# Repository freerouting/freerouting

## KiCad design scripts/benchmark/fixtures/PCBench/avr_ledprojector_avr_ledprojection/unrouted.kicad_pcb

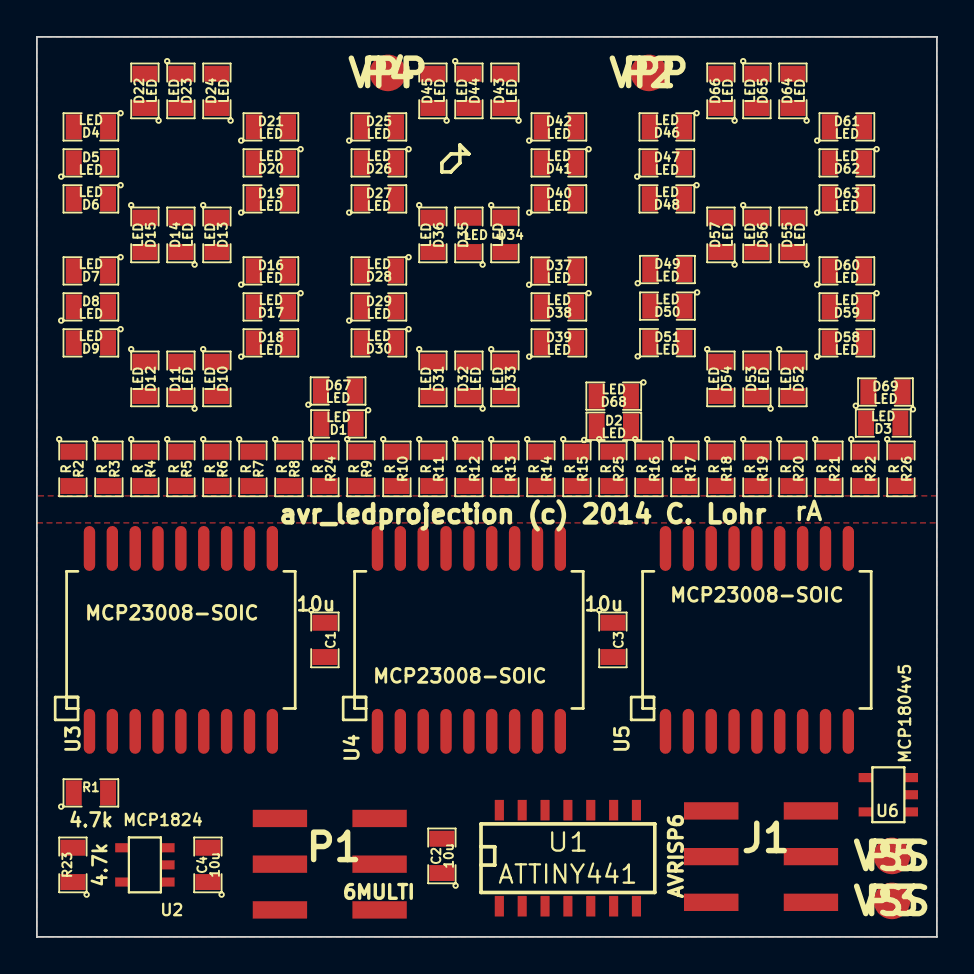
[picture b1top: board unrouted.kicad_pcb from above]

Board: 2 copper layers, 50.0 x 50.0 mm, 111 parts (0 on the bottom side), 104 nets, no tracks yet.

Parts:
C1, C2, C3, C4: 10u; SM0805
D1, D2, D3, D4, D5, D6, D7, D8, D9, D10, D11, D12, D13, D14, D15, D16, D17, D18, D19, D20, D21, D22, D23, D24, D25, D26, D27, D28, D29, D30, D31, D32, D33, D34, D35, D36, D37, D38, D39, D40, D41, D42, D43, D44, D45, D46, D47, D48, D49, D50, D51, D52, D53, D54, D55, D56, D57, D58, D59, D60, D61, D62, D63, D64, D65, D66, D67, D68, D69: LED; SM0805
J1: AVRISP6; RIBBON6SMT
P1: 6MULTI; RIBBON6SMT
P2, P4: VPP; .1SMTPIN
P3, P5: VSS; .1SMTPIN
R1, R23: 4.7k; SM0805
R2, R3, R4, R5, R6, R7, R8, R9, R10, R11, R12, R13, R14, R15, R16, R17, R18, R19, R20, R21, R22, R24, R25, R26: R; SM0805
U1: ATTINY441; SO14E
U2: MCP1824; SOT23-5
U3, U4, U5: MCP23008-SOIC; SOIC18-750
U6: MCP1804v5; SOT23-5

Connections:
+3.3V: C4.1, P1.4, R1.1, R23.1, U2.5
+5V: C1.1, C2.1, C3.1, J1.2, P1.2, U1.1, U2.1, U2.3, U3.4, U3.6, U3.18, U4.5, U4.6, U4.18, U5.6, U5.18, U6.5
GND: C1.2, C2.2, C3.2, C4.2, J1.6, P1.6, P3.1, P5.1, U1.14, U2.2, U3.3, U3.5, U3.9, U4.3, U4.4, U4.9, U5.3, U5.4, U5.5, U5.9, U6.2
unnamed: R9.2, U4.17
unnamed: R11.2, U4.15
unnamed: R22.2, U5.11
unnamed: R20.2, U5.13
unnamed: R18.2, U5.15
unnamed: R16.2, U5.17
unnamed: R4.2, U3.15
unnamed: R2.2, U3.17
unnamed: D3.1, D69.2
unnamed: R15.2, U4.11
unnamed: R25.2, U4.10
unnamed: D3.2, R26.1
unnamed: R26.2, U5.10
unnamed: D2.2, R25.1
unnamed: R7.2, U3.12
unnamed: D1.2, R24.1
unnamed: R24.2, U3.10
unnamed: J1.4, U1.7
unnamed: R21.2, U5.12
unnamed: P1.5, U1.11
unnamed: J1.1, U1.8
unnamed: R8.2, U3.11
unnamed: J1.5, U1.4
unnamed: J1.3, U1.9
unnamed: D2.1, D68.2
unnamed: D1.1, D67.2
unnamed: D44.2, D45.1
unnamed: D45.2, R15.1
unnamed: D46.2, D47.1
unnamed: D47.2, D48.1
unnamed: D43.2, D44.1
unnamed: D48.2, R16.1
unnamed: D49.2, D50.1
unnamed: D50.2, D51.1
unnamed: D51.2, R17.1
unnamed: R13.2, U4.13
unnamed: D36.2, R12.1
unnamed: R12.2, U4.14
unnamed: D37.2, D38.1
unnamed: D38.2, D39.1
unnamed: D39.2, R13.1
unnamed: R17.2, U5.16
unnamed: D40.2, D41.1
unnamed: D41.2, D42.1
unnamed: D42.2, R14.1
unnamed: R14.2, U4.12
unnamed: D60.2, R20.1
unnamed: D61.2, D62.1
unnamed: D62.2, D63.1
unnamed: D63.2, R21.1
unnamed: D64.2, D65.1
unnamed: D65.2, D66.1
unnamed: D66.2, R22.1
unnamed: D52.2, D53.1
unnamed: D53.2, D54.1
unnamed: D54.2, R18.1
unnamed: D55.2, D56.1
unnamed: D56.2, D57.1
unnamed: D57.2, R19.1
unnamed: R19.2, U5.14
unnamed: D58.2, D59.1
unnamed: D59.2, D60.1
unnamed: D13.2, D14.1
unnamed: D14.2, D15.1
unnamed: D15.2, R5.1
unnamed: R5.2, U3.14
unnamed: D12.2, R4.1
unnamed: D16.2, D17.1
unnamed: D17.2, D18.1
unnamed: D18.2, R6.1
unnamed: R6.2, U3.13
unnamed: D4.2, D5.1
unnamed: D5.2, D6.1
unnamed: D6.2, R2.1
unnamed: D7.2, D8.1
unnamed: D19.2, D20.1
unnamed: D8.2, D9.1
unnamed: D9.2, R3.1
unnamed: D10.2, D11.1
unnamed: D11.2, D12.1
unnamed: D28.2, D29.1
unnamed: D29.2, D30.1
unnamed: D30.2, R10.1
unnamed: R10.2, U4.16
unnamed: D31.2, D32.1
unnamed: D32.2, D33.1
unnamed: D33.2, R11.1
unnamed: D34.2, D35.1
unnamed: D35.2, D36.1
unnamed: D20.2, D21.1
unnamed: D21.2, R7.1
unnamed: D22.2, D23.1
unnamed: D23.2, D24.1
unnamed: D24.2, R8.1
unnamed: D25.2, D26.1
unnamed: D26.2, D27.1
unnamed: D27.2, R9.1
unnamed: R3.2, U3.16
SCL: P1.3, R23.2, U1.13, U3.1, U4.1, U5.1
SDA: P1.1, R1.2, U1.12, U3.2, U4.2, U5.2
VPP: D4.1, D7.1, D10.1, D13.1, D16.1, D19.1, D22.1, D25.1, D28.1, D31.1, D34.1, D37.1, D40.1, D43.1, D46.1, D49.1, D52.1, D55.1, D58.1, D61.1, D64.1, D67.1, D68.1, D69.1, P2.1, P4.1, U6.1, U6.4

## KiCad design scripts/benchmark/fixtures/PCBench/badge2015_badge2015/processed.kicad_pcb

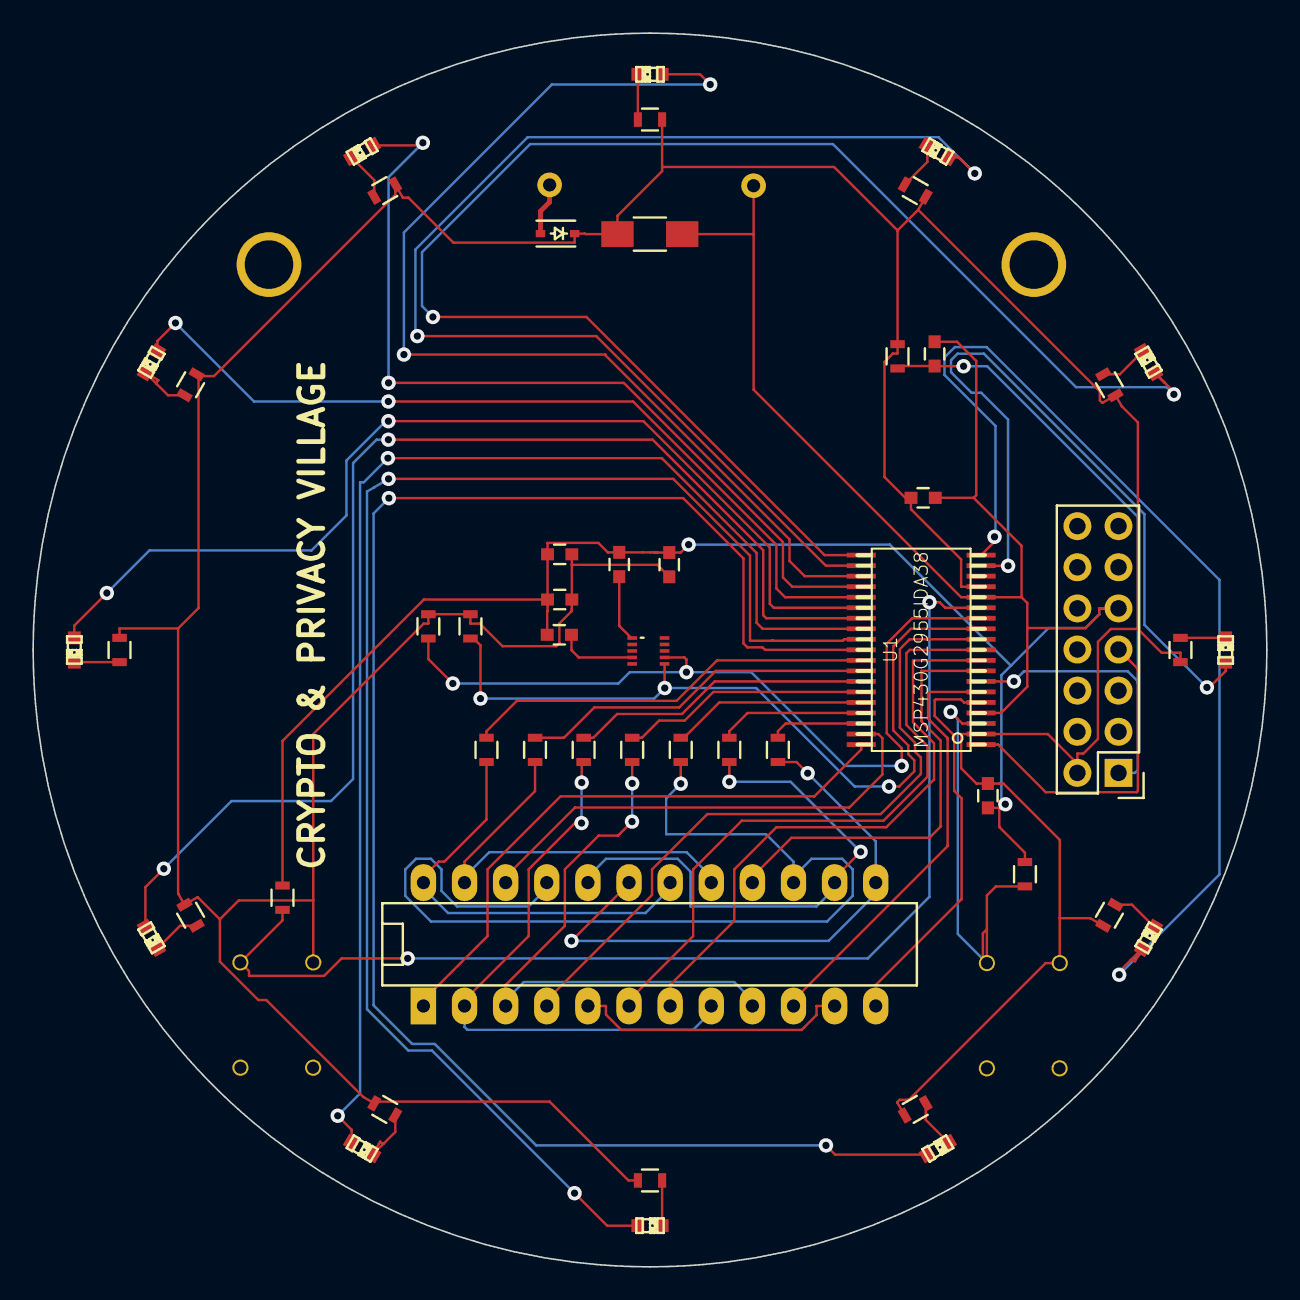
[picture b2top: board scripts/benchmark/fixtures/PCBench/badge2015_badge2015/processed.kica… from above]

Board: 2 copper layers, 76.2 x 76.2 mm, 55 parts (1 on the bottom side), 58 nets.

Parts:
2.2nF1: C; C_0603
BT1: Battery
C1, C2: 0.1uf; C_0603
C6: 47uF; C_1206_HandSoldering
C7: 1uf; C_0603
C8, C9, C10, C11: 100nf; C_0603
D1, D2, D3, D4, D5, D6, D7, D8, D9, D10, D11, D12: LED; LED-0603
D55: DIODE; SOD-323
MAG: MAG3110_10VFDFN
P1: CONN_01X14; Pin_Header_Straight_2x07
R1, R2, R3, R4, R5, R6, R7, R8, R9, R10, R11, R12: 499; R_0603
R13, R23: R; R_0603
R14, R15, R16, R17, R18, R21, R22: 680; R_0603
R19, R20: 4.7k; R_0603
R24: 47k; R_0603
SW1, SW2: SW_PUSH; push_btn
U1: MSP430G2955IDA38; AB2_TSSOP38_W
U4: 7SEGMENT; DIP-24__300_ELL
hole_l: hole
hole_r: hole_r; hole

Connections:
/3.3V: C1.1, C2.1, C6.1, C7.1, C8.1, C11.1, D55.2, P1.2, R1.1, R2.1, R3.1, R4.1, R5.1, R6.1, R7.1, R8.1, R9.1, R10.1, R11.1, R12.1, R19.1, R20.1, R24.1, SW1.1, SW2.1, U1.2, U1.16
/ANODE_a: R14.2, U4.12, U4.24
/ANODE_b: R15.2, U4.11, U4.23
/ANODE_c: R17.2, U4.3, U4.15
/ANODE_d: R21.2, U4.8, U4.20
/ANODE_dp: U4.5, U4.17
/ANODE_e: R16.2, U4.2, U4.14
/ANODE_f: R18.2, U4.9, U4.21
/ANODE_g: R22.2, U4.7, U4.19
/BAT+: BT1.1, D55.1
/CATHODE_1: U1.38, U4.1
/CATHODE_2: U1.37, U4.10
/CATHODE_3: U1.11, U4.4
/CATHODE_4: U1.10, U4.6
/CATHODE_5: U1.9, U4.13
/CATHODE_6: U1.8, U4.22
/CATHODE_7: U1.6, U4.16
/CATHODE_8: U1.5, U4.18
/P1(0): R15.1, U1.31
/P1(1): R16.1, U1.32
/P1(2): R17.1, U1.33
/P1(3): R18.1, U1.34
/P1(4): R21.1, U1.35
/P1(5): R22.1, U1.36
/P2(3): D2.2, U1.29
/P2(4): R14.1, U1.30
/P2(5): R13.1, SW1.2, U1.3
/P3(3): R23.1, SW2.2, U1.14
/P3(4): D10.2, U1.25
/P3(5): D11.2, U1.26
/P3(6): D12.2, U1.27
/P3(7): D1.2, U1.28
/P4(1): D4.2, U1.18
/P4(2): D3.2, U1.19
/P4(3): D5.2, U1.20
/P4(4): D6.2, U1.21
/P4(5): D7.2, U1.22
/P4(6): D8.2, U1.23
/P4(7): D9.2, U1.24
/SBWTCK: P1.7, U1.1
/SCL: MAG.7, R20.2, U1.13
/SDA: MAG.6, R19.2, U1.12
/~RST: 2.2nF1.1, P1.1, R24.2, U1.7
GND: 2.2nF1.2, BT1.2, C1.2, C2.2, C6.2, C7.2, C8.2, C9.1, C10.2, C11.2, P1.9, R13.2, R23.2, U1.4, U1.15
unnamed: C9.2, MAG.1
unnamed: C10.1, MAG.4
unnamed: D1.1, R1.2
unnamed: D2.1, R2.2
unnamed: D3.1, R3.2
unnamed: D4.1, R4.2
unnamed: D5.1, R5.2
unnamed: D6.1, R6.2
unnamed: D7.1, R7.2
unnamed: D8.1, R8.2
unnamed: D9.1, R9.2
unnamed: D10.1, R10.2
unnamed: D11.1, R11.2
unnamed: D12.1, R12.2

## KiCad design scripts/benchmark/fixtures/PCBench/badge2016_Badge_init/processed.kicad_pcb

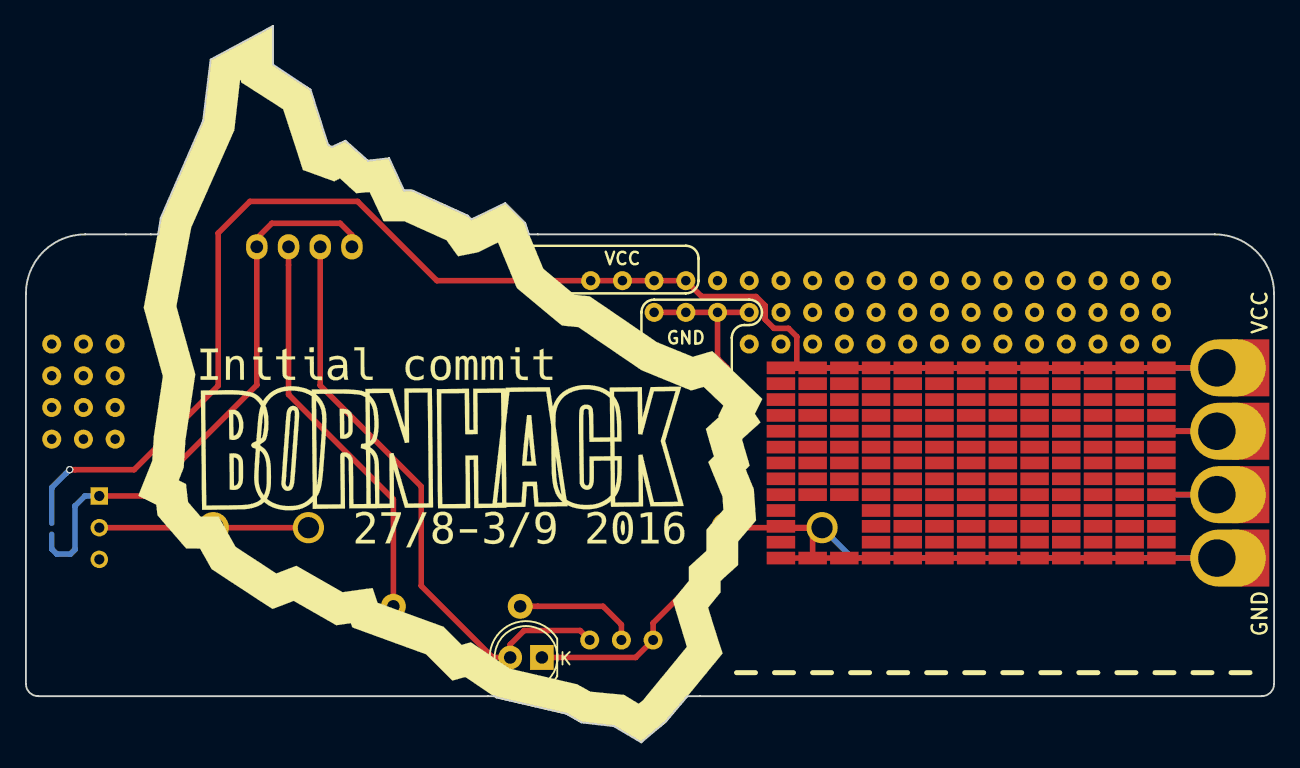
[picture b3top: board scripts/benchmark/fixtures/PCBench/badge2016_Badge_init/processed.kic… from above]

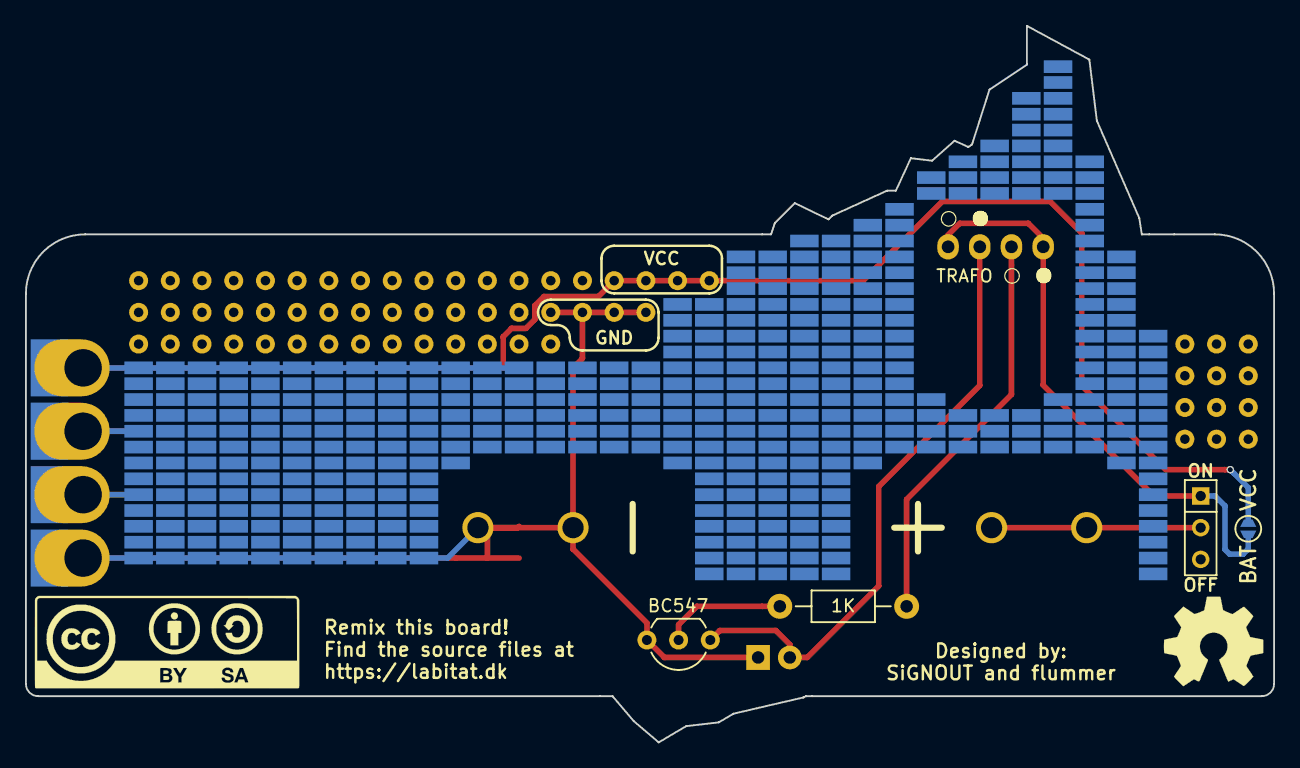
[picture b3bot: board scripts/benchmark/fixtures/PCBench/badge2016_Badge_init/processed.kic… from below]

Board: 2 copper layers, 100.0 x 57.4 mm, 9 parts (6 on the bottom side), 6 nets.

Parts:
BT1: Battery; BK-92
D1: LED; LED-5MM
JP1: Jumper_NC_Small; Solder_Jumper
P1, P2: CONN_01X01; PTH_Edge_Proto_Connector
Q1: BC547; TO-92_Inline_Wide
R1: 1K; Resistor_Horizontal_RM10mm
SW1: POWER; SW_Micro_SPST
T1: TRAFO; Pin_Header_Straight_1x04

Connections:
+BATT: JP1.1, SW1.1, T1.1, T1.4
GND: BT1.2, D1.1, Q1.3
unnamed: BT1.1, SW1.2
unnamed: D1.2, Q1.1, T1.3
unnamed: Q1.2, R1.2
unnamed: R1.1, T1.2

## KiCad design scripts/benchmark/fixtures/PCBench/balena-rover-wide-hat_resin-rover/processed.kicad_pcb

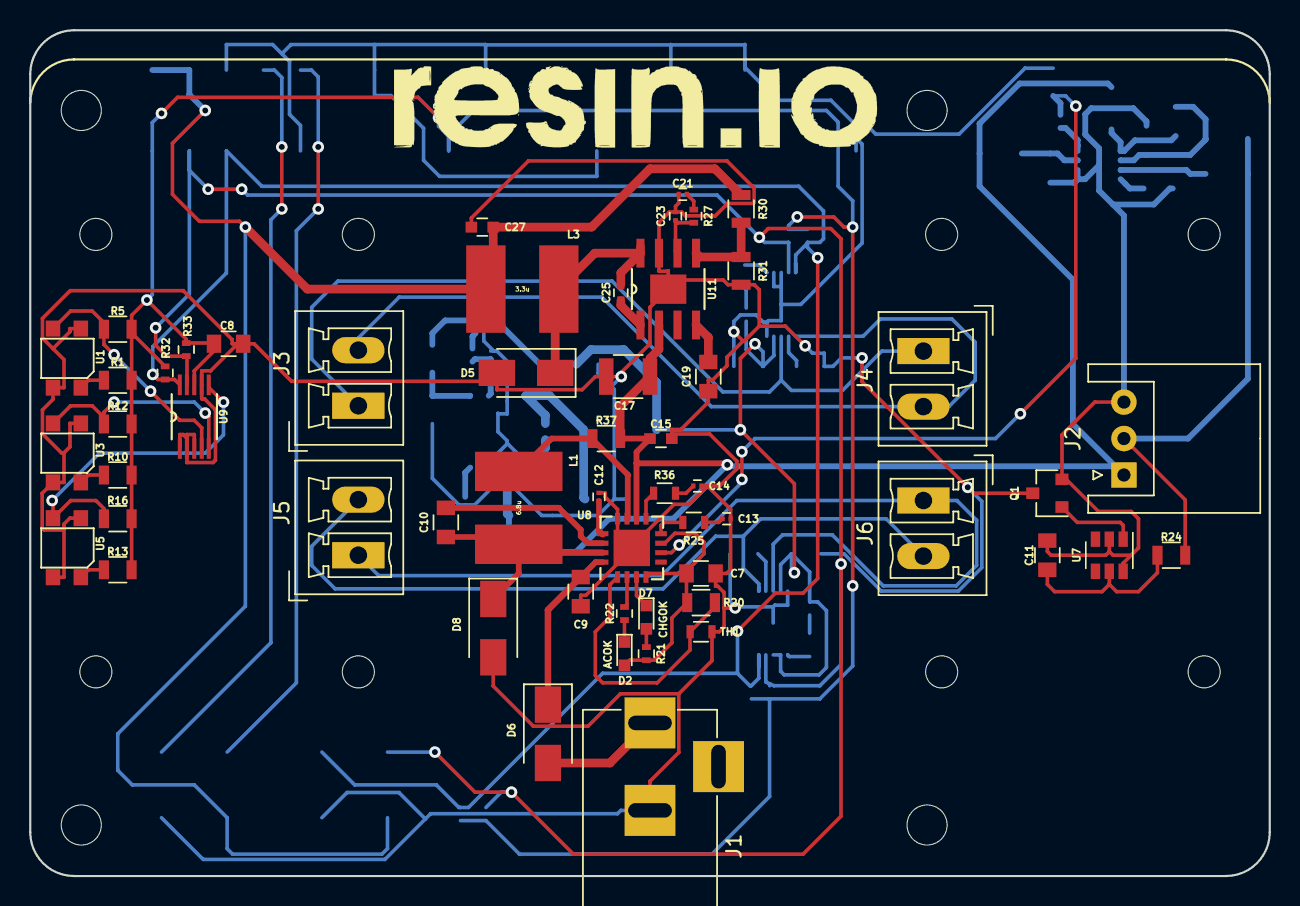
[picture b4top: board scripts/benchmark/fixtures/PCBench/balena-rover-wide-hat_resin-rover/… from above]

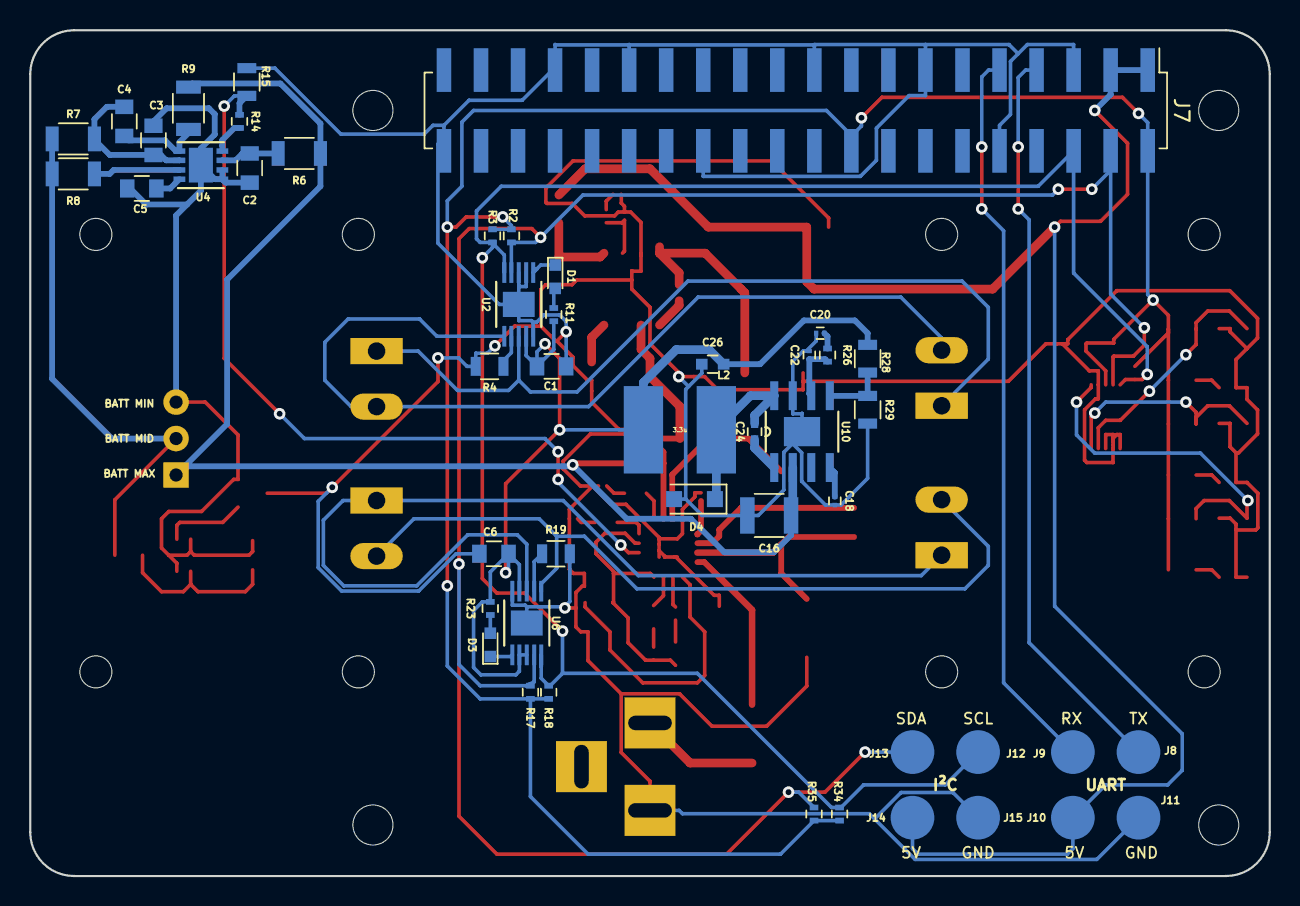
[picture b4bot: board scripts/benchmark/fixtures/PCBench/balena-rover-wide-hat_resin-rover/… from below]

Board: 2 copper layers, 85.0 x 58.0 mm, 107 parts (48 on the bottom side), 64 nets.

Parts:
C1, C6: 10u; C_0805
C2, C3, C4, C5, C8, C10, C11: 0.1u; C_0805
C7: 1u; C_0805
C9: 4.7u; C_0805
C12: 0.1u; C_0201
C13, C14: 2.2n; C_0201
C15, C26, C27: 22u; C_0603
C16, C17: 22u; C_1210
C18: 27p; C_0201
C19: 30p; C_0805
C20: 1n; C_0201
C21: 1.2n; C_0201
C22, C23: 8.2n; C_0201
C24, C25: 100n; C_0402
D1, D2, D3, D7: LED; LED_0603
D4: D_Schottky; D_SOD-123F
D5: D_Schottky; D_SMA_Standard
D6, D8: Schottky; D_SMA_Standard
J1: BARREL_JACK
J2: 2S LIPO; JST_XH_S03B-XH-A_03x2.50mm_Angled
J3: FL; PhoenixContact_MCV-G_02x3.81mm_Vertical
J4: BL; PhoenixContact_MCV-G_02x3.81mm_Vertical
J5: FR; PhoenixContact_MCV-G_02x3.81mm_Vertical
J6: BR; PhoenixContact_MCV-G_02x3.81mm_Vertical
J7: CONN_02X20; Pin_Header_Straight_2x20_Pitch2.54mm_SMD
J8, J9, J10, J11, J12, J13, J14, J15: TEST_1P; Measurement_Point_Round-SMD-Pad_Big
L1: 6.8u; SRN6045
L2, L3: 3.3u; SRN6045
Noname_1, Noname_2, Noname_3, Noname_4: RPi_Hat_Mounting_Hole
Q1: 2N7002; SOT-23
R1, R10, R13: 100; R_0805
R2, R3, R14, R17, R18, R32, R33, R34, R35: 4.7K; R_0402
R4, R19: 0.2; R_0805
R5, R12, R15, R16, R20, R24, R28: 10K; R_0805
R6, R8, R9: 150; R_1206
R7: 240; R_1206
R11, R21, R22, R23: 1K; R_0402
R25: 2.49K; R_0603
R26: 30.1K; R_0402
R27: 26.7K; R_0402
R29: 1.54K; R_0805
R30: 10.5K; R_0805
R31: 2K; R_0805
R36: 750; R_0603
R37: 0.1; R_0805
TH1: NTC 10K; R_0603
U1, U3, U5: QRE1113GR; 4LEADSMD
U2, U6: DRV8830; SOP65P640X110-15N
U4: BQ29209; SON65P315X315X100-9N
U7: S-8261; SOT-23-6
U8: MP2610; QFN-16-1EP_4x4mm_Pitch0.65mm
U9: ADS1015; SOP50P490X110-10N
U10, U11: TPS54332; SOIC127P600X170-9N

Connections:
/3.3V: C8.2, J7.2, J7.18, R1.2, R2.2, R3.2, R5.2, R10.2, R12.2, R13.2, R16.2, R17.2, R18.2, R32.1, R33.2, R34.2, R35.2, U9.8
/5V: C27.2, J7.1, J7.3, J10.1, J14.1, L3.1, R30.2
/6V: C1.1, C6.1, C26.2, L2.1, R11.1, R23.2, R28.2, U2.4, U6.4, U6.7, U6.8
/ADC0: R5.1, U1.C, U9.4
/ADC1: R12.1, U3.C, U9.5
/ADC2: R16.1, U5.C, U9.6
/BATT_MID: J2.2, R7.2, R8.2, R24.2
/BATT_MIN: C2.2, C3.1, C5.2, C11.2, J2.3, Q1.2, U4.5, U4.6, U4.9, U7.2, U7.6
/CHG_EN: R14.2, R15.1, U8.6
/DO: Q1.1, U7.1
/VCC: D6.2, J1.1
/VSENSE_5V: R30.1, R31.2, U11.5
/VSENSE_6V: R28.1, R29.2, U10.5
/V_BATT: C15.2, C16.2, C17.2, J2.1, R6.1, R9.2, R37.1, U8.10, U10.2, U11.2
GND: C1.2, C6.2, C7.1, C8.1, C9.2, C12.1, C13.1, C14.1, C15.1, C16.1, C17.1, C18.1, C19.1, C20.1, C21.1, C22.1, C23.1, C26.1, C27.1, D4.2, D5.2, D8.2, J1.2, J7.5, J7.10, J7.13, J7.19, J7.26, J7.29, J7.33, J7.40, J11.1, J15.1, Q1.3, R4.2, R15.2, R19.2, R29.1, R31.1, TH1.2, U1.E, U1.K, U2.5, U2.7, U2.8, U2.11, U3.E, U3.K, U5.E, U5.K, U6.5, U6.11, U8.12, U8.17, U9.1, U9.2, U9.3, U9.7, U10.7, U10.9, U11.7, U11.9
unnamed: C2.1, R6.2, U4.7
unnamed: C3.2, C4.2, R7.1, U4.2
unnamed: C4.1, R9.1, U4.1
unnamed: C5.1, U4.4
unnamed: C7.2, D2.2, R20.2, R21.1, U8.4, U8.7
unnamed: C9.1, D6.1, U8.16
unnamed: C10.1, D8.1, L1.2, U8.15
unnamed: C10.2, U8.14
unnamed: C11.1, R24.1, U7.5
unnamed: C12.2, U8.13
unnamed: C13.2, R25.1
unnamed: C14.2, R36.1
unnamed: C18.2, U10.4
unnamed: C19.2, U11.4
unnamed: C20.2, R26.1
unnamed: C21.2, R27.1
unnamed: C22.2, R26.2, U10.6
unnamed: C23.2, R27.2, U11.6
unnamed: C24.1, D4.1, L2.2, U10.8
unnamed: C24.2, U10.1
unnamed: C25.1, D5.1, L3.2, U11.8
unnamed: C25.2, U11.1
unnamed: D1.1, U2.6
unnamed: D1.2, R11.2
unnamed: D2.1, R22.2
unnamed: D3.1, U6.6
unnamed: D3.2, R23.1
unnamed: D7.1, U8.3
unnamed: D7.2, R21.2
unnamed: J3.1, J4.1, U2.3
unnamed: J3.2, J4.2, U2.1
unnamed: J5.1, J6.1, U6.3
unnamed: J5.2, J6.2, U6.1
unnamed: L1.1, R37.2, U8.11
unnamed: R1.1, U1.A
unnamed: R4.1, U2.2
unnamed: R8.1, U4.3
unnamed: R10.1, U3.A
unnamed: R13.1, U5.A
unnamed: R14.1, U4.8
unnamed: R19.1, U6.2
unnamed: R20.1, TH1.1, U8.1
unnamed: R22.1, U8.2
unnamed: R25.2, U8.8
unnamed: R36.2, U8.9
RX: J7.9, J9.1
SCL: J7.6, J12.1, R3.1, R18.1, R32.2, R34.1, U2.10, U6.10, U9.10
SDA: J7.4, J13.1, R2.1, R17.1, R33.1, R35.1, U2.9, U6.9, U9.9
TX: J7.7, J8.1

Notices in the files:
scripts/benchmark/fixtures/PCBench/avr_ledprojector_avr_ledprojection/unrouted.kicad_pcb:
avr_ledprojection (c) 2014 C. Lohr
